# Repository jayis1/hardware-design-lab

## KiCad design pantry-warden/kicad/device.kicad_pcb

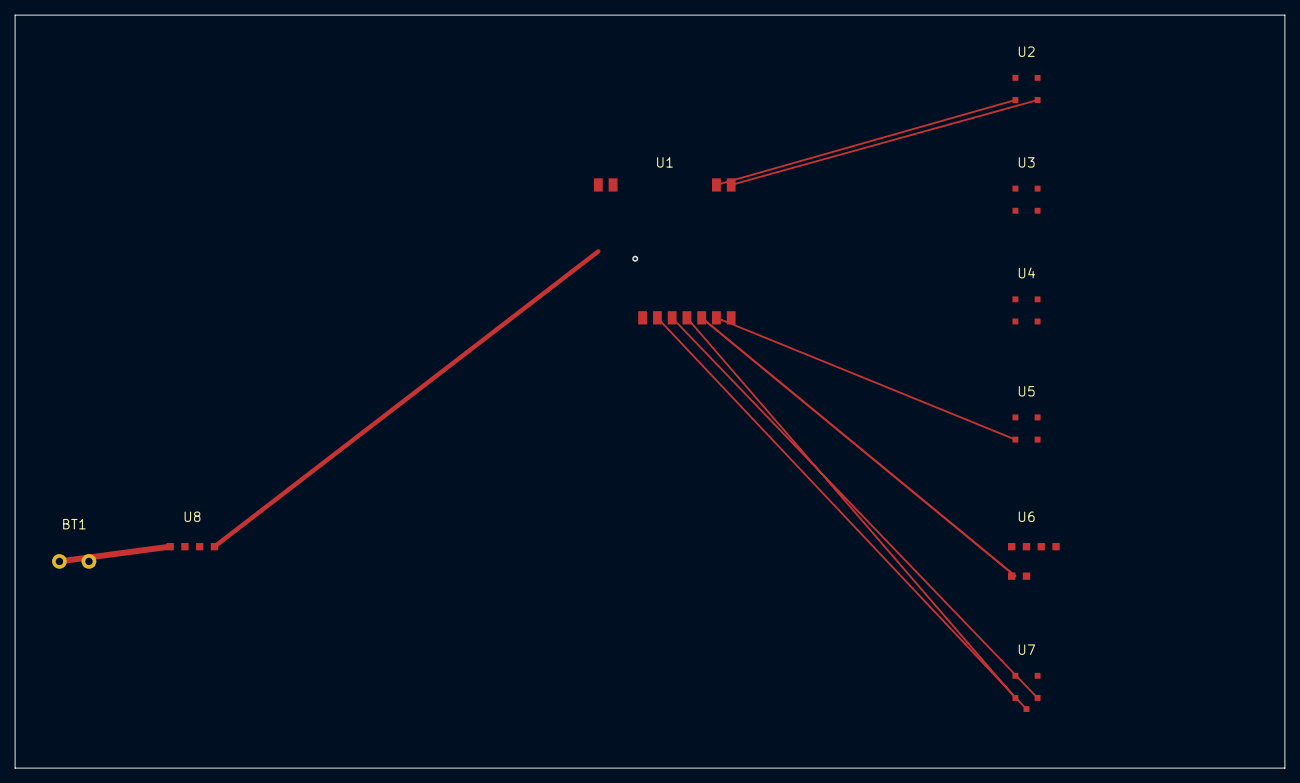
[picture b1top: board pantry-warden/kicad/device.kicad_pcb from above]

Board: 2 copper layers, 172.0 x 102.0 mm, 9 parts (0 on the bottom side), 9 nets.

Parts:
BT1: Li-Ion Pack; Battery_Pack
U1: ESP32-S3-WROOM-1
U2: SCD41
U3: SGP41
U4: AS7341
U5: VL53L4CD
U6: NAU7802
U7: ICS-43434
U8: BQ25895

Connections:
3V3: U1.1, U2.1, U3.1, U4.1, U5.1, U6.1, U7.1
GND: BT1.2, U1.2, U2.2, U3.2, U4.2, U5.2, U6.2, U6.6, U7.2, U8.3
I2C_SCL: U1.3, U2.3, U3.3, U4.3, U5.3, U6.3
I2C_SDA: U1.4, U2.4, U3.4, U4.4, U5.4, U6.4
MIC_SCK: U1.9, U7.4
MIC_SD: U1.8, U7.3
MIC_WS: U1.10, U7.5
PIEZO_ADC: U1.7, U6.5
VBAT: BT1.1, U8.1, U8.2

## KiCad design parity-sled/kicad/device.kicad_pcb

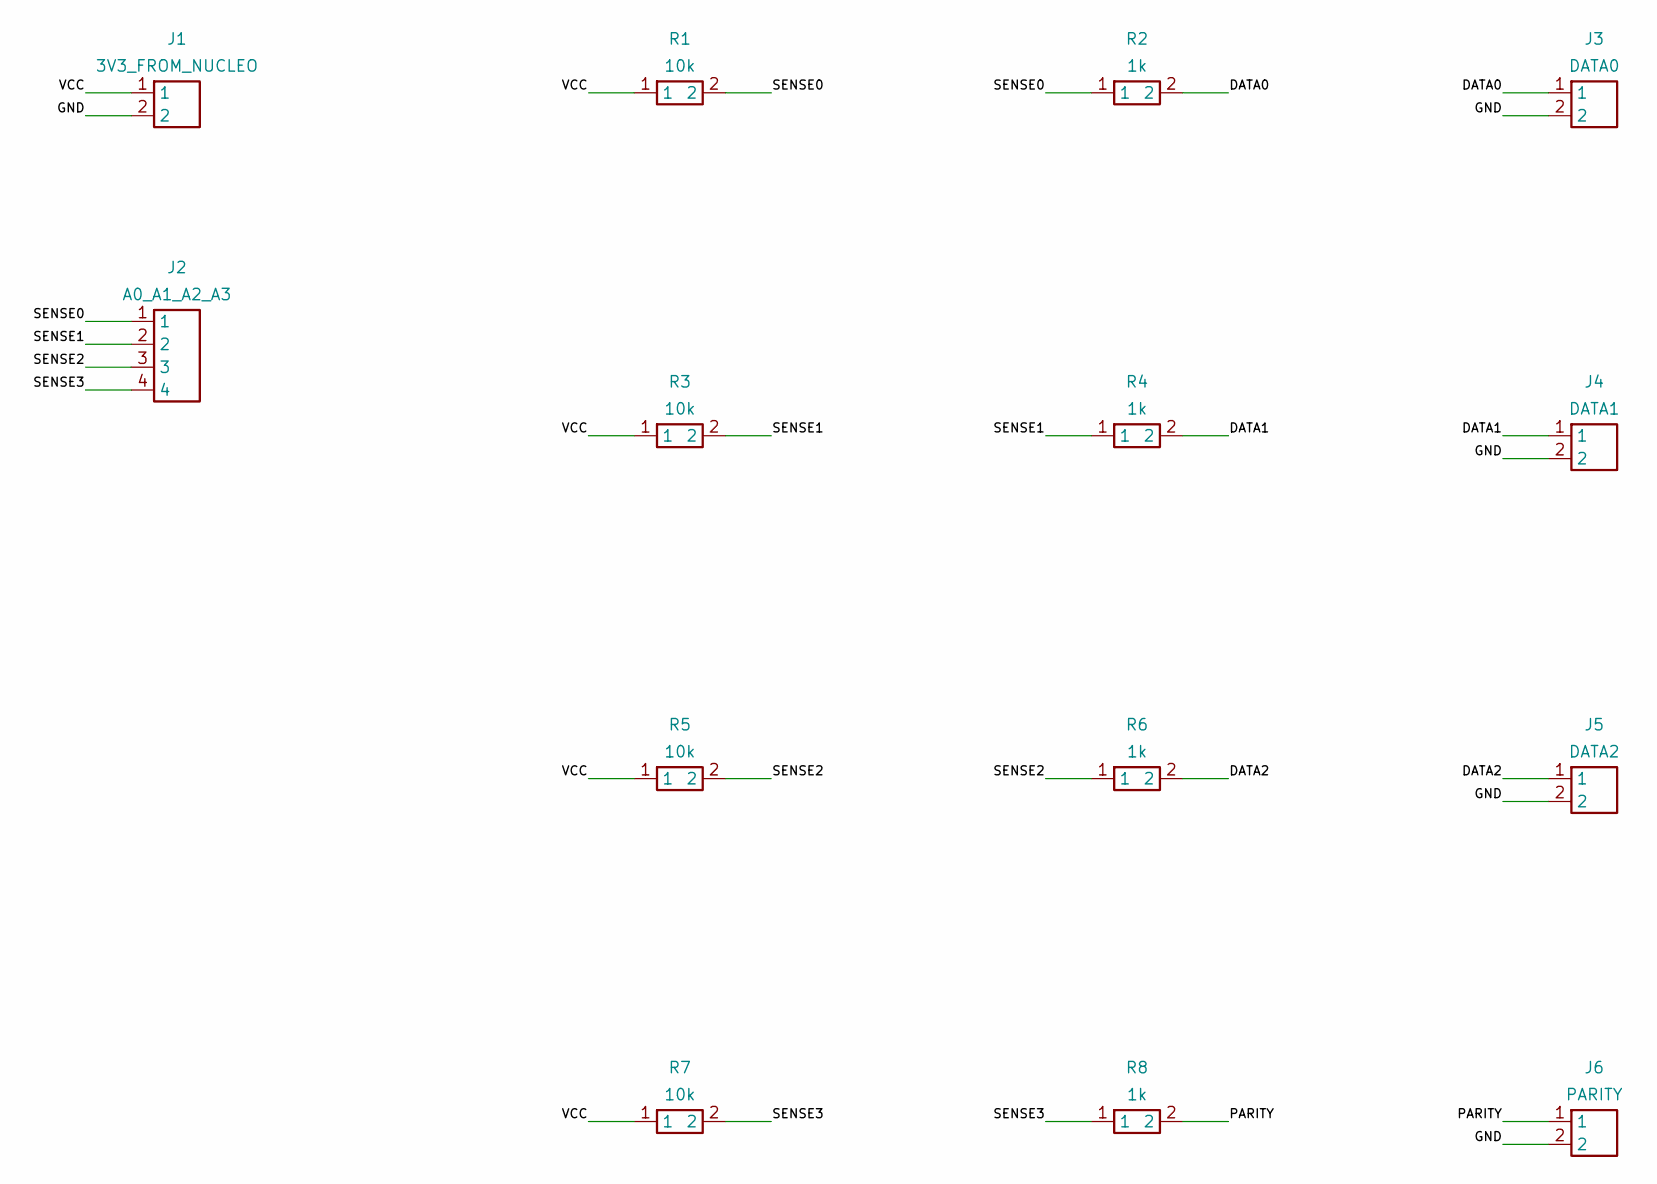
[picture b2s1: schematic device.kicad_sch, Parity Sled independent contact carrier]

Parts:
J1: 3V3_FROM_NUCLEO; PinHeader_1x02_P2.54mm_Vertical
J2: A0_A1_A2_A3; PinHeader_1x04_P2.54mm_Vertical
J3: DATA0; PinHeader_1x02_P2.54mm_Vertical
J4: DATA1; PinHeader_1x02_P2.54mm_Vertical
J5: DATA2; PinHeader_1x02_P2.54mm_Vertical
J6: PARITY; PinHeader_1x02_P2.54mm_Vertical
R1, R3, R5, R7: 10k; R_Axial_DIN0207_L6.3mm_D2.5mm_P7.62mm_Horizontal
R2, R4, R6, R8: 1k; R_Axial_DIN0207_L6.3mm_D2.5mm_P7.62mm_Horizontal

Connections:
DATA0: J3.1, R2.2
DATA1: J4.1, R4.2
DATA2: J5.1, R6.2
GND: J1.2, J3.2, J4.2, J5.2, J6.2
PARITY: J6.1, R8.2
SENSE0: J2.1, R1.2, R2.1
SENSE1: J2.2, R3.2, R4.1
SENSE2: J2.3, R5.2, R6.1
SENSE3: J2.4, R7.2, R8.1
VCC: J1.1, R1.1, R3.1, R5.1, R7.1

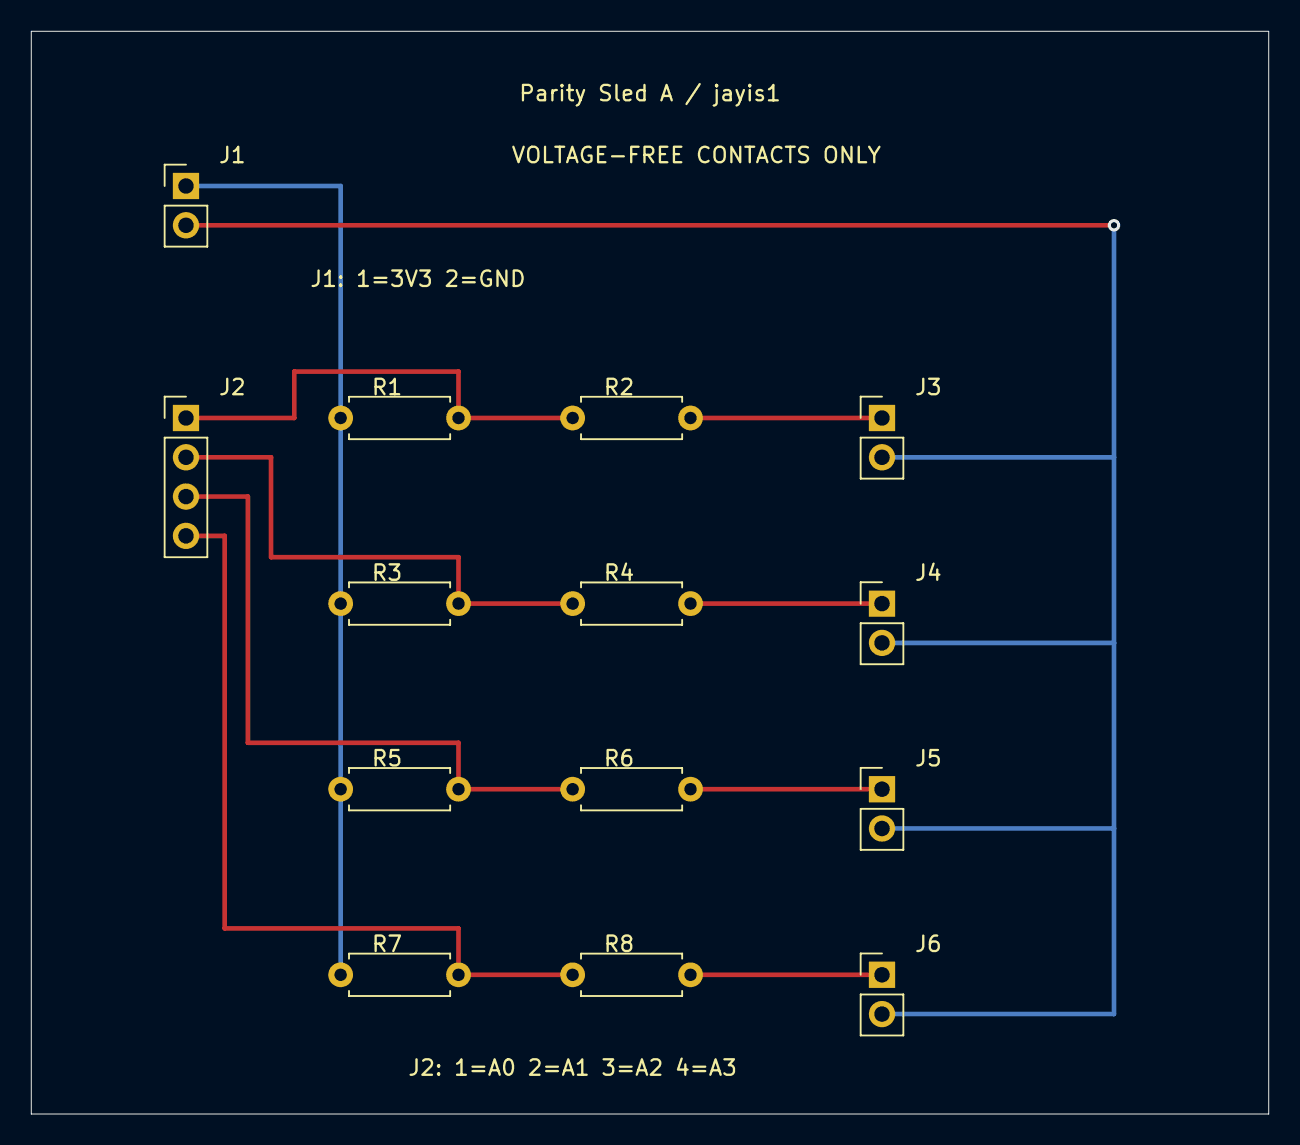
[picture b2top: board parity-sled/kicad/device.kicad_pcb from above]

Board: 2 copper layers, 80.0 x 70.0 mm, 14 parts (0 on the bottom side), 10 nets.

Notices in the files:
pantry-warden/kicad/device.kicad_sch:
Copyright (C) 2026 jayis1
